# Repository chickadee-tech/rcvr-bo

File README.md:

# Chickadee Tech Receiver Breakout Polystack Mod #
This is a breakout board designed for connecting a variety of Remote Control receivers to the control board. It supports Serial RX, PPM and PPM along with telemetry.

## Documentation ##
See the [wiki](https://github.com/chickadee-tech/rcvr-bo/wiki) for documentation.

## Polystack ##
This **mod** board is part of the Polystack platform for modular microcontrol systems. More information on the platform can be found at [polystack.org](http://polystack.org).

## Support ##
If you need support with a board you own or have development questions please email support@chickadee.tech or check [chickadee.tech/support](https://chickadee.tech/support) for other ways to get support.

## Contributing ##
Please note that this project is released with a [Contributor Code of Conduct](CODE_OF_CONDUCT.md). By participating in this project you agree to abide by its terms.

### Setup ###
Components and footprints for PCB parts are not included in this repository. Instead, checkout the [chickadee-tech/kicad-libs](https://github.com/chickadee-tech/kicad-libs) repository in the same directory that this repository is checked out in. All part definitions should be relative so that they will load correctly.

### Pull requests ###
For fixes please submit a pull request to the original repository. After the pull request is merged, check the [Chickadee Tech Active Contributor Discount (ACD)](https://chickadee.tech/active-contributor) to see if you are eligible for a discount code to use on your next purchase.

### Derivatives ###
If developing your own version of the Receiver Breakout board please remove all Chickadee Tech trademarks and follow the [CC-BY license](LICENSE). While not required, please consider open sourcing your modifications so others can learn from your improvements. If you do email support@chickadee.tech and we may choose to add your project to the ACD.

You may also license the Polystack logo for free by emailing support@chickadee.tech. We'll ask for your gerbers to ensure the design complies with specifications laid out [here](https://github.com/chickadee-tech/polystack/wiki) and provide written permission to use the trademark after compliance has been demonstrated.

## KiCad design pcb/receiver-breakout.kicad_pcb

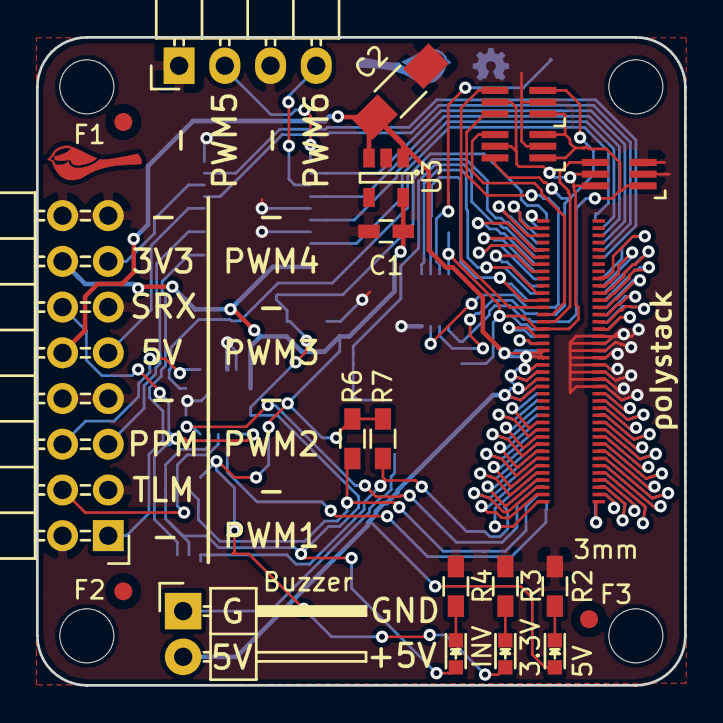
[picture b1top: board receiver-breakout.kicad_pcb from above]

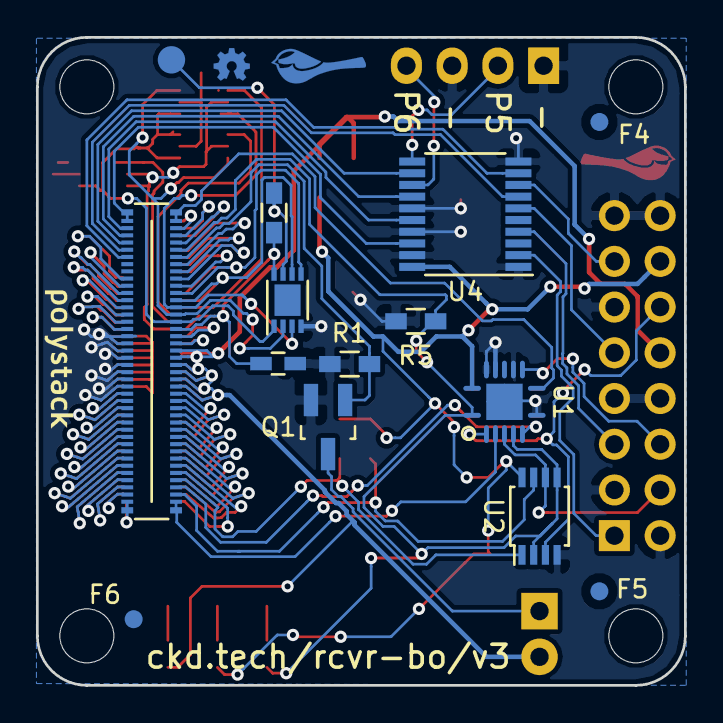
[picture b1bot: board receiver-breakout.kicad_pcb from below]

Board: 2 copper layers, 36.0 x 36.0 mm, 37 parts (15 on the bottom side), 84 nets.

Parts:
C1: 1uF; C_0603_HandSoldering
C2: 10uF; C_1206_HandSoldering
D2: Green; LED_0603
D3: Yellow; LED_0603
D4: Red; LED_0603
F1, F2, F3, F4, F5, F6: 1mm; Fiducial
P1: CONN_02X08; Pin_Header_Angled_2x08
P2: CONN_01X02; Pin_Header_Angled_1x02
P3: CONN_01X04; Pin_Header_Angled_1x04
PORT_ANDOR1: SN74LVC1G0832; SC-70-6_Handsoldering
PORT_C1: 0.1uF; C_0603_HandSoldering
PORT_IC1: AT24CS02-MAHM; DFN-8-1EP_3x2mm_Pitch0.5mm
PORT_IN1: CKD_SANDWICH; DF40-80pin-Header
PORT_INV1: SN74LVC1G58; SC-70-6_Handsoldering
PORT_OUT1: CKD_SANDWICH; DF40-3-4mm-80pin-Receptacle
PORT_P1: CONN_01X01; Measurement_Point_Round-SMD-Pad_Small
PORT_R1: 10k; R_0603_HandSoldering
PORT_XOR1: SN74LVC1G58; SC-70-6_Handsoldering
Q1: Q_NMOS_GSD; SOT-23_Handsoldering
R1, R5, R6, R7: 10K; R_0603_HandSoldering
R2, R3, R4: 1k; R_0603_HandSoldering
U1: 74LS86; QFN-14-3.5x3.5mm
U2: 74AHC2G125; TSSOP-8_3x3mm_Pitch0.65mm
U3: TLV70233DBV; SOT-23-5
U4: 74LS244; TSSOP-20_4.4x6.5mm_Pitch0.65mm
svg2mod, svg2mod#2: G***; polystack-bold-0.4

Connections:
+5V: C2.1, D2.2, P1.10, P2.2, PORT_IN1.19, PORT_IN1.20, PORT_IN1.21, PORT_IN1.22, PORT_IN1.23, PORT_IN1.24, PORT_OUT1.19, PORT_OUT1.20, PORT_OUT1.21, PORT_OUT1.22, PORT_OUT1.23, PORT_OUT1.24, U3.1, U3.3
/ExpansionPort/3V3_0.3A_E: PORT_IN1.17, PORT_OUT1.17
/ExpansionPort/3V3_0.3A_LL: PORT_ANDOR1.5, PORT_C1.1, PORT_IC1.8, PORT_IN1.16, PORT_INV1.5, PORT_INV1.6, PORT_OUT1.16, PORT_R1.2, PORT_XOR1.5
/ExpansionPort/+BATT: PORT_IN1.18, PORT_OUT1.18
/ExpansionPort/ADC1: PORT_IN1.49, PORT_OUT1.49
/ExpansionPort/ADC2: PORT_IN1.50, PORT_OUT1.50
/ExpansionPort/BOOT: PORT_IN1.65, PORT_OUT1.65
/ExpansionPort/CAN_HI: PORT_IN1.67, PORT_OUT1.67
/ExpansionPort/CAN_LO: PORT_IN1.68, PORT_OUT1.68
/ExpansionPort/GPIO1: D4.2, PORT_IN1.5, R5.1, U1.1, U1.5, U2.2, U2.5
/ExpansionPort/GPIO2: PORT_IN1.6, Q1.1, R1.1
/ExpansionPort/GPIO3: PORT_IN1.7, PORT_OUT1.5
/ExpansionPort/GPIO4: PORT_IN1.8, PORT_OUT1.6
/ExpansionPort/GPIO5: PORT_IN1.9, PORT_OUT1.7
/ExpansionPort/GPIO6: PORT_IN1.10, PORT_OUT1.8
/ExpansionPort/HEIGHT_1: PORT_ANDOR1.1, PORT_IC1.1, PORT_IN1.15, PORT_INV1.1, PORT_XOR1.1, PORT_XOR1.3
/ExpansionPort/HEIGHT_2: PORT_ANDOR1.3, PORT_IC1.2, PORT_IN1.14, PORT_XOR1.6
/ExpansionPort/HEIGHT_4: PORT_ANDOR1.6, PORT_IC1.3, PORT_IN1.13
/ExpansionPort/NEW_HEIGHT_1: PORT_INV1.4, PORT_OUT1.15
/ExpansionPort/NEW_HEIGHT_2: PORT_OUT1.14, PORT_XOR1.4
/ExpansionPort/NEW_HEIGHT_4: PORT_ANDOR1.4, PORT_OUT1.13
/ExpansionPort/RESET: PORT_IN1.66, PORT_OUT1.66
/ExpansionPort/SDMMC1_CK: PORT_IN1.55, PORT_OUT1.55
/ExpansionPort/SDMMC1_CMD: PORT_IN1.56, PORT_OUT1.56
/ExpansionPort/SDMMC1_D0: PORT_IN1.51, PORT_OUT1.51
/ExpansionPort/SDMMC1_D1: PORT_IN1.52, PORT_OUT1.52
/ExpansionPort/SDMMC1_D2: PORT_IN1.53, PORT_OUT1.53
/ExpansionPort/SDMMC1_D3: PORT_IN1.54, PORT_OUT1.54
/ExpansionPort/SPI1_MISO: PORT_IN1.79, PORT_OUT1.79
/ExpansionPort/SPI1_MOSI: PORT_IN1.80, PORT_OUT1.80
/ExpansionPort/SPI1_NSS: PORT_IN1.77, PORT_OUT1.77
/ExpansionPort/SPI1_SCK: PORT_IN1.78, PORT_OUT1.78
/ExpansionPort/SPI2_MISO: PORT_IN1.75, PORT_OUT1.75
/ExpansionPort/SPI2_MOSI: PORT_IN1.76, PORT_OUT1.76
/ExpansionPort/SPI2_NSS: PORT_IN1.73, PORT_OUT1.73
/ExpansionPort/SPI2_SCK: PORT_IN1.74, PORT_OUT1.74
/ExpansionPort/SPI3_MISO: PORT_IN1.71, PORT_OUT1.71
/ExpansionPort/SPI3_MOSI: PORT_IN1.72, PORT_OUT1.72
/ExpansionPort/SPI3_NSS: PORT_IN1.69, PORT_OUT1.69
/ExpansionPort/SPI3_SCK: PORT_IN1.70, PORT_OUT1.70
/ExpansionPort/TIM1: PORT_IN1.1, U1.8
/ExpansionPort/TIM2: PORT_IN1.2, PORT_OUT1.1
/ExpansionPort/TIM3: PORT_IN1.3, PORT_OUT1.2
/ExpansionPort/TIM4: PORT_IN1.4, PORT_OUT1.3
/ExpansionPort/TIMG1_CH1: PORT_IN1.41, U4.18
/ExpansionPort/TIMG1_CH2: PORT_IN1.42, U4.16
/ExpansionPort/TIMG1_CH3: PORT_IN1.43, U4.14
/ExpansionPort/TIMG1_CH4: PORT_IN1.44, U4.12
/ExpansionPort/TIMG2_CH1: PORT_IN1.45, U4.7
/ExpansionPort/TIMG2_CH2: PORT_IN1.46, U4.9
/ExpansionPort/UART1_RX: PORT_IN1.40, U1.3
/ExpansionPort/UART1_TX: PORT_IN1.39, R6.2, U2.7
/ExpansionPort/UART2_RX: PORT_IN1.38, U1.6
/ExpansionPort/UART2_TX: PORT_IN1.37, R7.2, U2.1
/ExpansionPort/UART3_RX: PORT_IN1.36, PORT_OUT1.40
/ExpansionPort/UART3_TX: PORT_IN1.35, PORT_OUT1.39
/ExpansionPort/UART4_RX: PORT_IN1.34, PORT_OUT1.38
/ExpansionPort/UART4_TX: PORT_IN1.33, PORT_OUT1.37
/ExpansionPort/UART5_RX: PORT_IN1.32, PORT_OUT1.36
/ExpansionPort/UART5_TX: PORT_IN1.31, PORT_OUT1.35
/ExpansionPort/UART6_RX: PORT_IN1.30, PORT_OUT1.34
/ExpansionPort/UART6_TX: PORT_IN1.29, PORT_OUT1.33
/ExpansionPort/UART7_RX: PORT_IN1.28, PORT_OUT1.32
/ExpansionPort/UART7_TX: PORT_IN1.27, PORT_OUT1.31
/ExpansionPort/UART8_RX: PORT_IN1.26, PORT_OUT1.30
/ExpansionPort/UART8_TX: PORT_IN1.25, PORT_OUT1.29
/ExpansionPort/i2c_SCL: PORT_IC1.6, PORT_IN1.12, PORT_OUT1.12
/ExpansionPort/i2c_SDA: PORT_IC1.5, PORT_IN1.11, PORT_OUT1.11
/PPM: P1.6, U1.9
/PWM1: P1.1, U4.2
/PWM2: P1.5, U4.4
/PWM3: P1.9, U4.6
/PWM4: P1.13, U4.8
/PWM5: P3.2, U4.11
/PWM6: P3.4, U4.13
/RC: P1.12, U1.2, U2.3
/TELEM: P1.4, U1.4, U2.6
GND: C1.2, C2.2, P1.2, P1.3, P1.7, P1.8, P1.11, P1.15, P1.16, P3.1, P3.3, PORT_ANDOR1.2, PORT_C1.2, PORT_IC1.4, PORT_IN1.57, PORT_IN1.58, PORT_IN1.59, PORT_IN1.60, PORT_IN1.61, PORT_IN1.62, PORT_IN1.63, PORT_IN1.64, PORT_INV1.2, PORT_INV1.3, PORT_OUT1.57, PORT_OUT1.58, PORT_OUT1.59, PORT_OUT1.60, PORT_OUT1.61, PORT_OUT1.62, PORT_OUT1.63, PORT_OUT1.64, PORT_XOR1.2, Q1.2, R1.2, R2.2, R3.2, R4.2, R5.2, U1.7, U1.10, U1.12, U1.13, U2.4, U3.2, U4.1, U4.10, U4.15, U4.17, U4.19
unnamed: D2.1, R2.1
unnamed: D3.1, R3.1
unnamed: D4.1, R4.1
unnamed: P2.1, Q1.3
unnamed: PORT_IC1.7, PORT_P1.1, PORT_R1.1
VCC: C1.1, D3.2, P1.14, R6.1, R7.1, U1.14, U2.8, U3.5, U4.20

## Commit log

2016-02-07 Initial work on receiver breakout to support receivers without cradles.
2016-03-05 Receiver Breakout v1 which should support all receivers that Cleanflight does.
2016-04-07 Unknown changes to receiver breakout.
2016-04-13 Rebrand everything to Polystack and increment versions.
2016-04-16 Final gerbers for test manufacturing run.
2016-06-07 Update polystack logo to bold variant, connect i2c lines to eeprom and bump version number.
2016-07-07 Add license information to many files. PCB design files are CC-BY and code is MIT license.
2016-07-07 Add back .gitignore after repo split.
2016-07-07 Convert to relative component and footprint paths.
2016-07-09 Correct README description.

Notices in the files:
pcb/receiver-breakout.kicad_pcb:
Copyright 2016 Chickadee Tech LLC
This work is licensed under the Creative Commons Attribution 4.0 International License.
To view a copy of this license, visit http://creativecommons.org/licenses/by/4.0
or send a letter to Creative Commons, PO Box 1866, Mountain View, CA 94042, USA.
